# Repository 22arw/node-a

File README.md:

# Node-A Cruiser Maintenance Management for Wichita
## About this project
This project will improve cruiser maintenance tracking for the Wichita Police department. To better maintain our Wichita Police cruisers, an OBD-II compatible device connects to and monitors each cruiser. The device utilizes a LoRaWAN network within Wichita to send realtime notifications and data through gateways to a central server which can then be displayed on dashboards for the department. In order to utilize the LoRaWAN network, we’ll make use of the Protocol Buffers method of serializing data into small packets. We may divide the data into multiple packets sent periodically to meet the LoRaWAN duty cycle standard. Once the Server group has set up a network server, we’ll work to create a windows application that will display statistics from all cruisers and notify the maintenance department when maintenance is due. 
## Pinout
The pinout for the MKRCAN sheild, Adafruit Feather 32u4, ODB2 connector, and LED is listed below.

| DESC           | MKRCAN | Feather   | ODB2 | LED |
|----------------|--------|-----------|------|-----|
| CAN CS         | 3      | 6         |      |     |
| INT            | 7      | SDA(1)    |      |     |
| MOSI           | 8      | MO        |      |     |
| SCK            | 9      | SCK       |      |     |
| MISO           | 10     | MI        |      |     |
| CPU POWER      | vcc    | 3v        |      |     |
| POWER TO F     | vin    | usb       |      |     |
| POWER FROM F   | 5v     | usb       |      |     |
| GND            | GND    | GND       |      |     |
| LED GND        |        | GND       |      | GND |
| Red            |        | 9         |      | R   |
| Green          |        | 10        |      | G   |
| Blue           |        | 11        |      | B   |
| POWER FROM CAR |        | 16        | VIN  |     |
| CAR CAN        |        | 6 (CANH)  | CANL |     |
| CAR CAN        |        | 14 (CANL) | CANH |     |
| GND            |        | 5         | GND  |     |

*The CAN library uses default CS and INT pins. To set different pins, use CAN.setPins(CS, INT).*

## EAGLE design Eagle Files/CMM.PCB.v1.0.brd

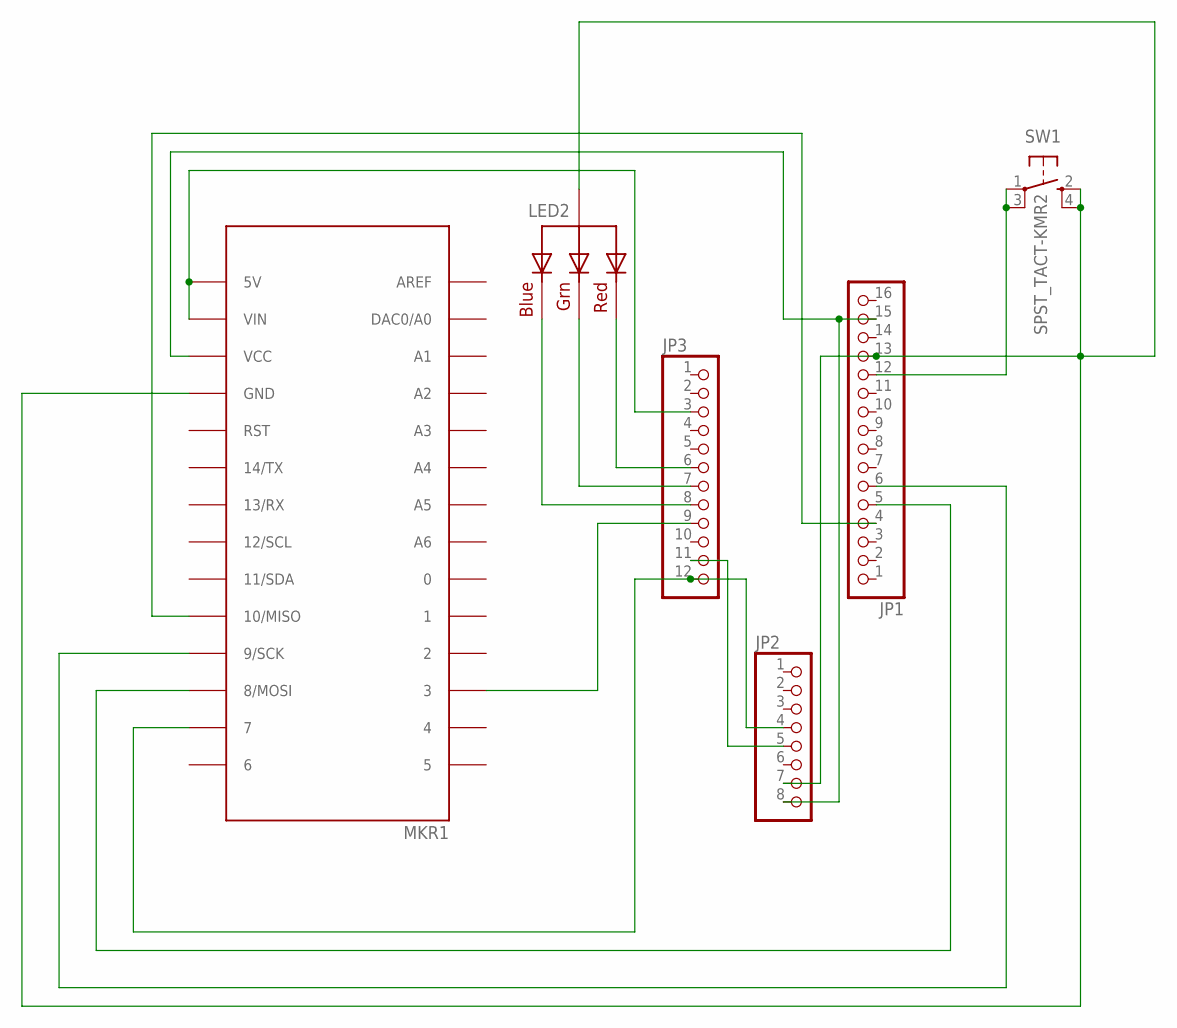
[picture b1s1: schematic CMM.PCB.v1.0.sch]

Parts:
JP1: HEADER-1X16ROUND; 1X16_ROUND
JP2: HEADER-1X870MIL; 1X08_ROUND_70
JP3: HEADER-1X12; 1X12_ROUND
LED2: RGBLED_CA-5MM; LED5MMRGB
MKR1: -; ARDUINO-UTILITY_MKRBOARD
SW1: SPST_TACT-KMR2; KMR2

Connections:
GND: JP1.13, JP2.7, LED2.2 (VCC), MKR1.GND, SW1.2 (S), SW1.4 (S1)
unnamed: JP3.9, MKR1.3
unnamed: JP2.4, JP3.12, MKR1.7
unnamed: JP1.5, MKR1.8 (8/MOSI)
unnamed: JP1.6, MKR1.9 (9/SCK)
unnamed: JP1.4, MKR1.10 (10/MISO)
unnamed: JP1.15, JP2.8, MKR1.VCC
unnamed: JP3.3, MKR1.5V, MKR1.VIN
unnamed: JP3.6, LED2.1 (RED)
unnamed: JP2.5, JP3.11
unnamed: JP3.7, LED2.3 (GREEN)
unnamed: JP3.8, LED2.4 (BLUE)
SIGNAL: JP1.12, SW1.1, SW1.3 (P1)

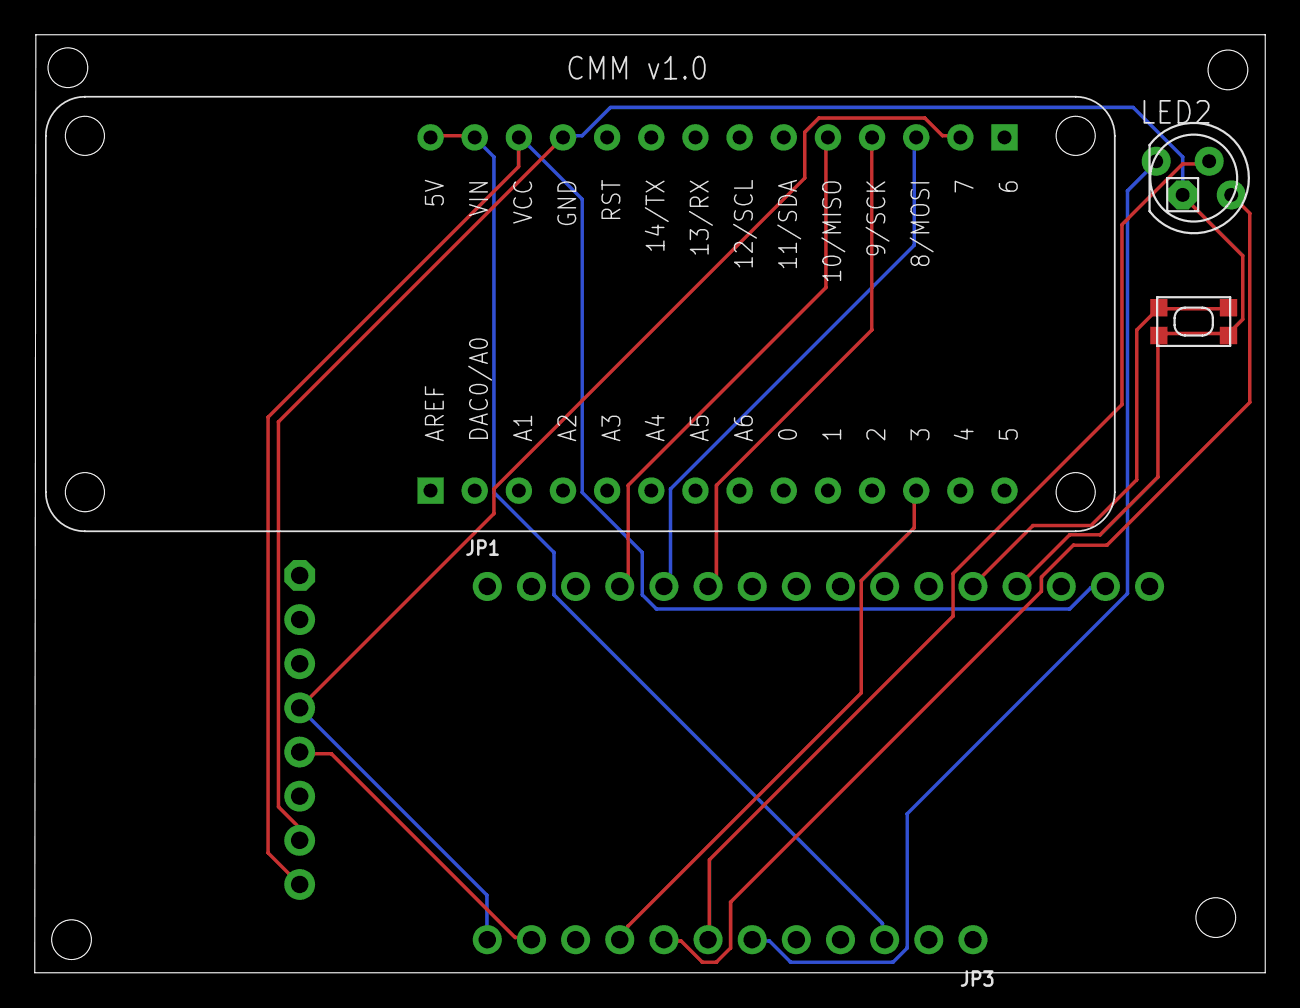
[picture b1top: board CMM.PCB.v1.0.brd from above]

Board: 2 copper layers, 70.8 x 54.0 mm, 6 parts (0 on the bottom side), 13 nets.

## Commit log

2021-01-12 Initial despot of code written last semester.
    This includes the car-device firmware and our development lora-serial relay code.
2021-02-15 Updated FRAM
2021-03-03 Update Corrected Schematic and Board files
2021-03-03 Change folder name
2021-03-07 Built housing shell and cap.
2021-03-07 Create tinylora_SubjectToChange
    This is an example sketch, but it already has the TTN keys set up
2021-03-07 An example sketch that has the TTN keys setup
2021-03-12 Board and Schematic files
2021-03-12 Added first semester housing.
2021-03-23 Built decoder.js
2021-03-29 Finished decoder script
2021-04-06 Range testing sample code
2021-04-12 Added encoding
2021-04-16 Modified for indoor (carless) testing
2021-04-16 Finished encoder / decoder testing
2021-04-26 Test Plan
2021-05-04 Added new housing.
2021-05-04 Added pushbutton test.

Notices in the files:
parts and their libraries:
microbuilder: This work is placed in the public domain, and may be freely used for commercial and non-commercial work with the following conditions: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
